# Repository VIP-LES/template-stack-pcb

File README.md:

# LEOS Stack PCB Template

This repository is the starting-point PCB template for VIP Lightning From the Edge of Space (LEOS). **All LEOS modules should be spun off from this template** so that every module begins with the standard Raspberry Pi Pico, CAN-FD network, stack connectors, board shape, and mechanical layout.

## Create a module repository from this template

Do not fork or clone this repository as the permanent home of a new module. Create a fresh repository from the public GitHub template instead:

1. Open this template repository on GitHub.
2. Select **Use this template**, then **Create a new repository**.
3. Choose the LEOS organization as the owner and enter the new module's repository name and description.
4. Leave **Include all branches** unchecked unless the module specifically needs work from non-default template branches.
5. Choose public visibility, then select **Create repository**.
6. Clone the newly created repository and open `LEOS-stack-template.kicad_pro` in KiCad.

GitHub also allows this template to be selected from the **Repository template** menu while creating a new repository. See GitHub's [repository template instructions](https://docs.github.com/en/repositories/creating-and-managing-repositories/creating-a-repository-from-a-template) for the current interface.

## Before designing

- Rename the root KiCad project, schematic, and PCB files for the module.
- Change the root sheet/page title in both the schematic and PCB. Rename or add schematic sheets so their names clearly describe each circuit domain.
- Update the **date** and **revision** in both the schematic and PCB Page Settings. These fields are used in the PCB silkscreen, so stale metadata will be manufactured onto the board.
- Replace the template title and delete the instructional text box on the root schematic once it is no longer needed.
- Use separate schematic sheets to isolate circuit domains, and document the design well enough for the schematic to explain itself.

## Design expectations

- Use [pinout.xyz](https://pinout.xyz/) with the Pico 2 view when selecting configurable pins. Avoid using SPI0 for other devices because it is reserved for the high-throughput CAN bus; SPI1, I2C0, and UART0 are exposed as starting interfaces.
- Keep the standard CAN-FD and stack-connector circuitry intact unless a reviewed module requirement calls for a change.
- Verify that every schematic symbol, PCB footprint, and selected BOM item agree. Record the manufacturer, manufacturer part number (MPN), and DigiKey information for each part.
- Prefer practical, hand-placeable packages such as SOIC, 0805, 1206, SOT, and TSSOP. Do not choose extremely small packages when a larger suitable option exists.
- Commit coherent, incremental changes with descriptive messages. Do not commit generated outputs, junk files, or Gerbers when they can be regenerated from the KiCad sources.
- Review the schematic, layout, footprints, sourcing, and manufacturer recommendations before ordering hardware.

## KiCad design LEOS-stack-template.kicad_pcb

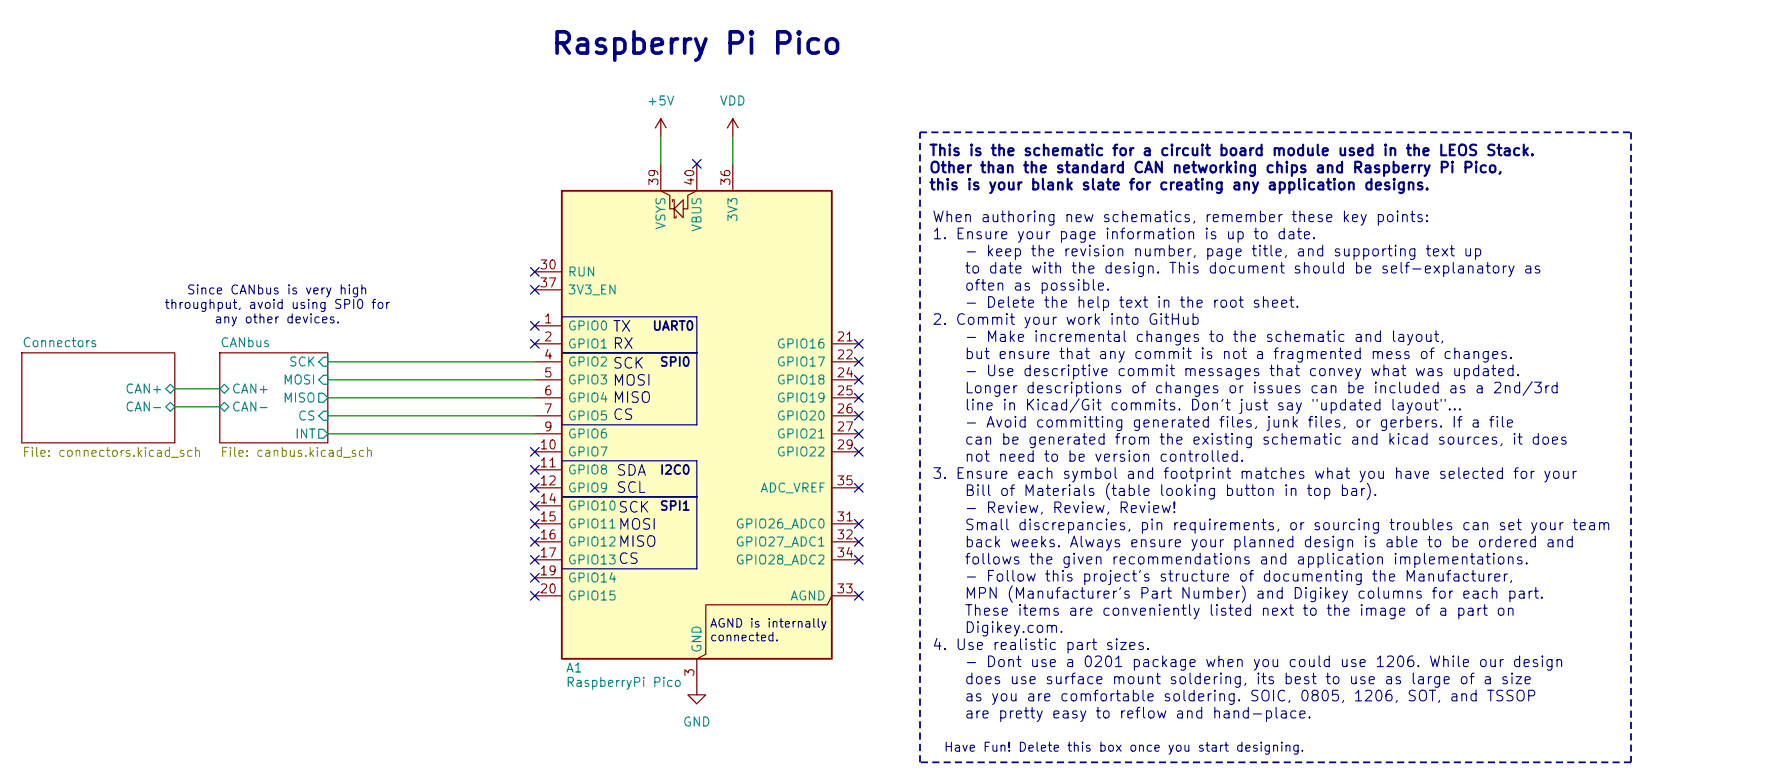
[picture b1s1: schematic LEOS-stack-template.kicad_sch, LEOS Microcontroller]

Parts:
A1: RaspberryPi Pico; RaspberryPi_Pico_Common_Unspecified; MPN PIM724; Digikey 1778-PIM724-ND

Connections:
+5V: A1.39 (VSYS); also elsewhere on the board
/CANbus/CS: A1.7 (GPIO5); also elsewhere on the board
/CANbus/INT: A1.9 (GPIO6); also elsewhere on the board
/CANbus/MISO: A1.6 (GPIO4); also elsewhere on the board
/CANbus/MOSI: A1.5 (GPIO3); also elsewhere on the board
/CANbus/SCK: A1.4 (GPIO2); also elsewhere on the board
GND: A1.3 (GND), A1.8 (GND), A1.13 (GND), A1.18 (GND), A1.23 (GND), A1.28 (GND), A1.38 (GND); also elsewhere on the board
VDD: A1.36 (3V3); also elsewhere on the board

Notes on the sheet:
This is the schematic for a circuit board module used in the LEOS Stack. Other than the standard CAN networking chips and Raspberry Pi Pico, this is your blank slate for creating any application designs.
SPI1
Raspberry Pi Pico
SCK MOSI MISO CS
Have Fun! Delete this box once you start designing.
Since CANbus is very high throughput, avoid using SPI0 for any other devices.
SPI0
SDA SCL
TX RX
When authoring new schematics, remember these key points: 1. Ensure your page information is up to date. - keep the revision number, page title, and supporting text up to date with the design. This document should be self-explanatory as often as possible. - Delete the help text in the root sheet. 2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
UART0
I2C0
AGND is internally connected.

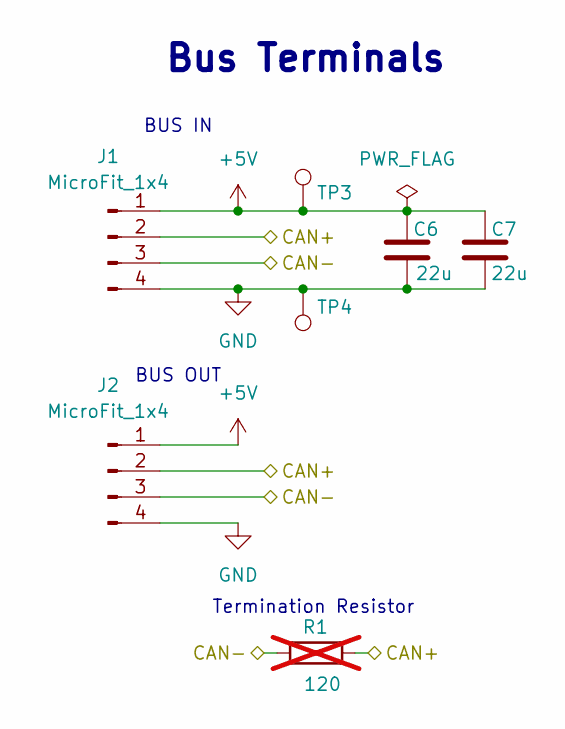
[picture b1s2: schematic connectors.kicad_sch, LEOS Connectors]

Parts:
C6, C7: 22u; C_1206_3216Metric; MPN CL31B226MPHNNNE; Digikey 1276-3148-1-ND
J1, J2: MicroFit_1x4; Molex_MicroFit3.0_43650-0410_1x04_Horizontal; MPN 0436500409; Digikey WM1882CT-ND
R1: 120; R_Axial_DIN0207_L6.3mm_D2.5mm_P7.62mm_Horizontal; MPN CF14JT120R; Digikey CF14JT120RCT-ND; not fitted
TP3: 5V Test Point; TestPoint_Loop_D2.60mm_Drill0.9mm_Beaded; MPN 5000; Digikey 36-5000-ND
TP4: GND Test Point; TestPoint_Loop_D2.60mm_Drill0.9mm_Beaded; MPN 5001; Digikey 36-5001-ND

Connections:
+5V: C6.1, C7.1, J1.1, J2.1, TP3.1 (1_1); also elsewhere on the board
/CANbus/CAN+: J1.2, J2.2, R1.2; also elsewhere on the board
/CANbus/CAN-: J1.3, J2.3, R1.1; also elsewhere on the board
GND: C6.2, C7.2, J1.4, J2.4, TP4.1 (1_1); also elsewhere on the board

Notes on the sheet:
BUS OUT
Bus Terminals
BUS IN
Termination Resistor

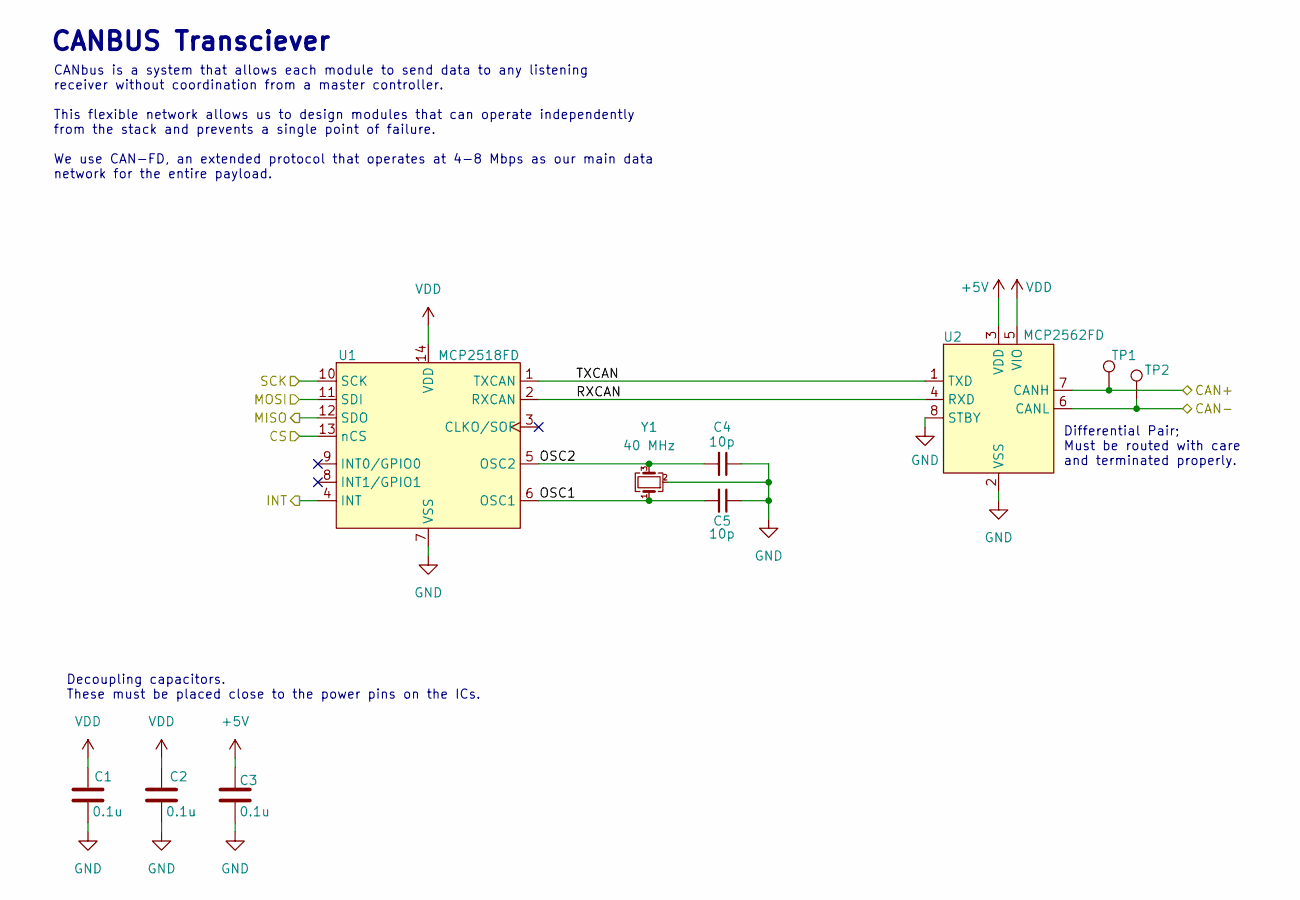
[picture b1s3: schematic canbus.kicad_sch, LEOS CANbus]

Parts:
C1, C2, C3: 0.1u; C_0805_2012Metric; MPN CL21B104KBCNNNC; Digikey 1276-1003-1-ND
C4, C5: 10p; C_0805_2012Metric; MPN CL21C100CBANNNC; Digikey 1276-2561-1-ND
TP1: CAN-H Test Point; TestPoint_Loop_D2.60mm_Drill0.9mm_Beaded; MPN 5004; Digikey 36-5004-ND
TP2: CAN-L Test Point; TestPoint_Loop_D2.60mm_Drill0.9mm_Beaded; MPN 5116; Digikey 36-5116-ND
U1: MCP2518FD; SOIC-14_3.9x8.7mm_P1.27mm; MPN MCP2518FDT-E/SL; LCSC C626758
U2: MCP2562FD; SOIC-8_3.9x4.9mm_P1.27mm; MPN MCP2562FDT-H/SN; LCSC C511335
Y1: 40 MHz; Crystal_SMD_2016-4Pin_2.0x1.6mm; MPN ECS-400-10-37B2-CKY-TR; Digikey 50-ECS-400-10-37B2-CKY-TRCT-ND

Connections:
+5V: C3.1, U2.3 (VDD); also elsewhere on the board
/CANbus/CAN+: TP1.1 (1_1), U2.7 (CANH); also elsewhere on the board
/CANbus/CAN-: TP2.1 (1_1), U2.6 (CANL); also elsewhere on the board
/CANbus/CS: U1.13 (nCS); also elsewhere on the board
/CANbus/INT: U1.4 (INT); also elsewhere on the board
/CANbus/MISO: U1.12 (SDO); also elsewhere on the board
/CANbus/MOSI: U1.11 (SDI); also elsewhere on the board
/CANbus/OSC1: C5.2, U1.6 (OSC1), Y1.1
/CANbus/OSC2: C4.2, U1.5 (OSC2), Y1.3
/CANbus/RXCAN: U1.2 (RXCAN), U2.4 (RXD)
/CANbus/SCK: U1.10 (SCK); also elsewhere on the board
/CANbus/TXCAN: U1.1 (TXCAN), U2.1 (TXD)
GND: C1.2, C2.2, C3.2, C4.1, C5.1, U1.7 (VSS), U2.2 (VSS), U2.8 (STBY), Y1.2 (G), Y1.4 (G); also elsewhere on the board
VDD: C1.1, C2.1, U1.14 (VDD), U2.5 (VIO); also elsewhere on the board

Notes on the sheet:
Differential Pair; Must be routed with care and terminated properly.
CANBUS Transciever
CANbus is a system that allows each module to send data to any listening receiver without coordination from a master controller. This flexible network allows us to design modules that can operate independently from the stack and prevents a single point of failure. We use CAN-FD, an extended protoco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
Decoupling capacitors. These must be placed close to the power pins on the ICs.

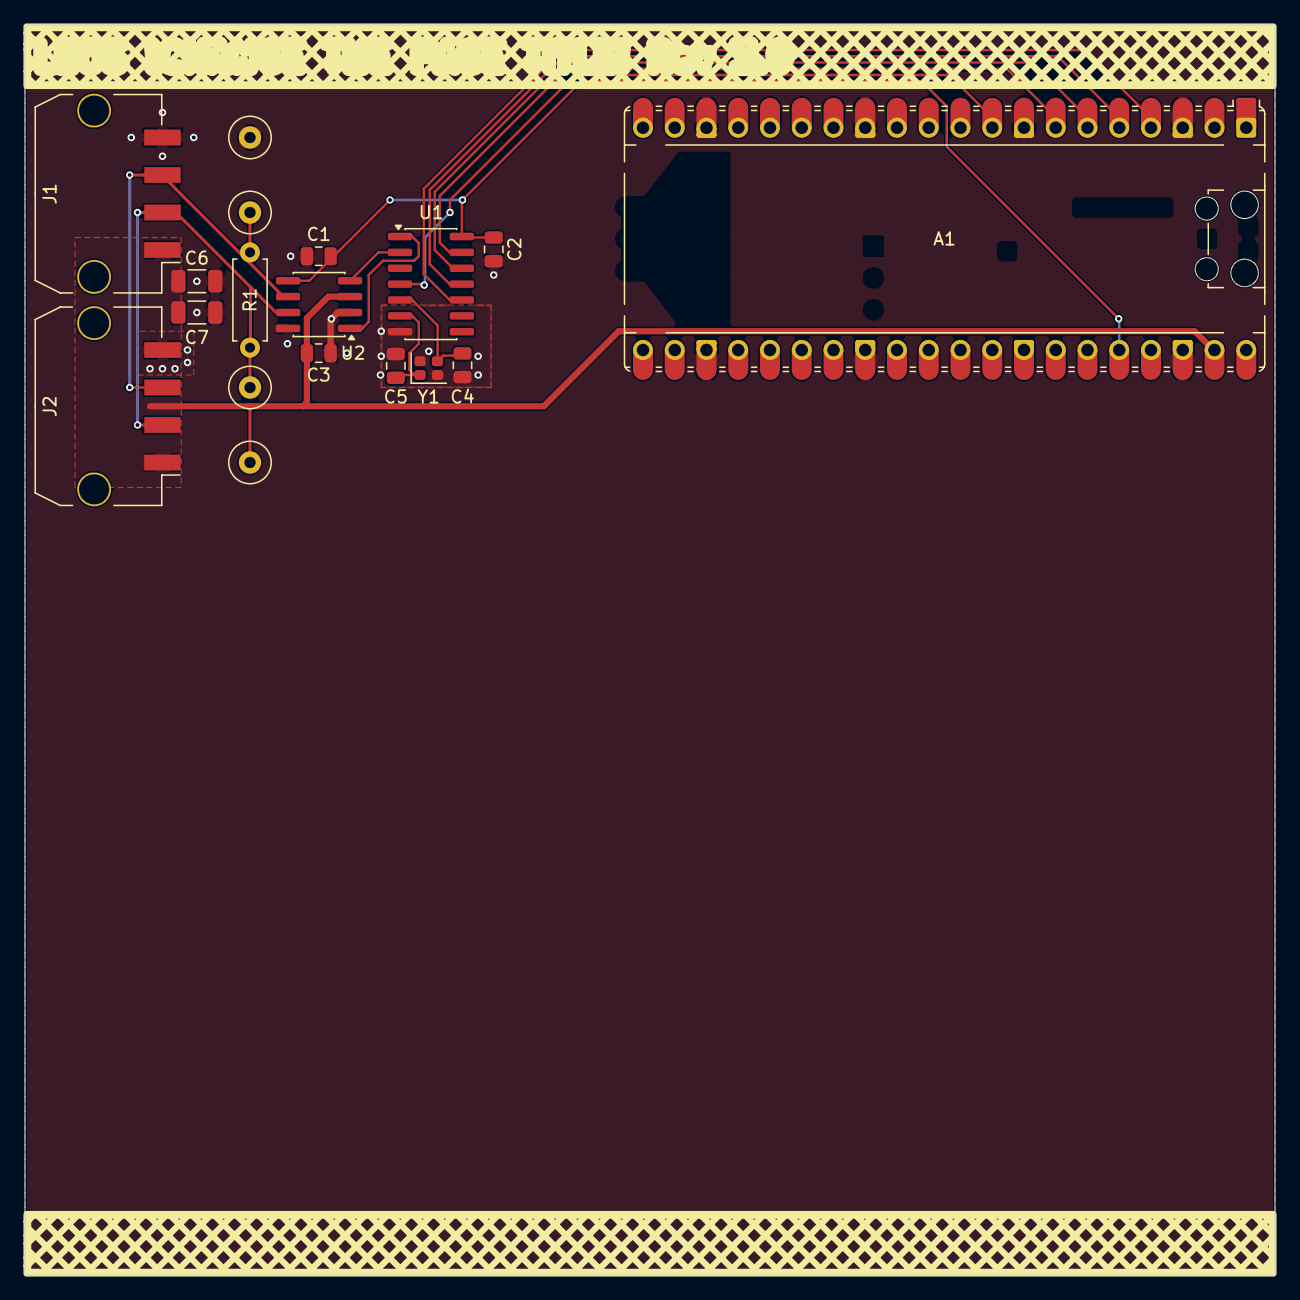
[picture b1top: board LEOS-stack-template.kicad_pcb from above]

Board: 2 copper layers, 100.0 x 100.0 mm, 18 parts (0 on the bottom side), 14 nets.

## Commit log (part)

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2025-09-09 Initial R1 Template PCB Design
2025-09-26 Redesigned Rev 2 fixing 0603 cap size and layout
2025-09-26 Clean up tracks to remove warnings
2026-02-15 New redesign featuring updated components, new sheets, better routing, and 100% 3D View
2026-02-16 Improved via placement, added LCSC part numbers.
2026-02-16 Updated routing for CANbus crystal. Should improve stencil process.
2026-02-16 Add drill origin, removed footprint locks, and cleaned up fab notes
2026-02-17 Add .gitignore for KiCad and common file types
    Add common file patterns to .gitignore for KiCad, backups, outputs, and OS junk.
